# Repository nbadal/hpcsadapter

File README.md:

Breakout Adapter for HP Common Slot Power Supplies
==================================================

This adapter board enables use of an HP (or HPE) Common Slot server power
supply with your 3D printer, cryptocurrency mining rig, etc.  These power
supplies are readily available on the used market at low prices (I've seen
460W models going for just $20) and are more reliable and deliver more power
than the power supplies commonly shipped with 3D printers.

Four pairs of screw terminals provide 12V when the switch is turned on.  A
USB power jack (5V 2.4A) is also provided that is always on when the power
supply is plugged in; this could be used to (for instance) power a Raspberry
Pi running OctoPrint to control your printer.

This project depends on these submodules:

- https://gitlab.com/salfter/kicad-libs
- https://gitlab.com/salfter/digikey-kicad-library

(The latter is a fork of the DigiKey KiCad library at GitHub, with 3D models
added as I need them.)

`git clone --recursive https://gitlab.com/salfter/hpcsadapter.git` should
pull in everything.

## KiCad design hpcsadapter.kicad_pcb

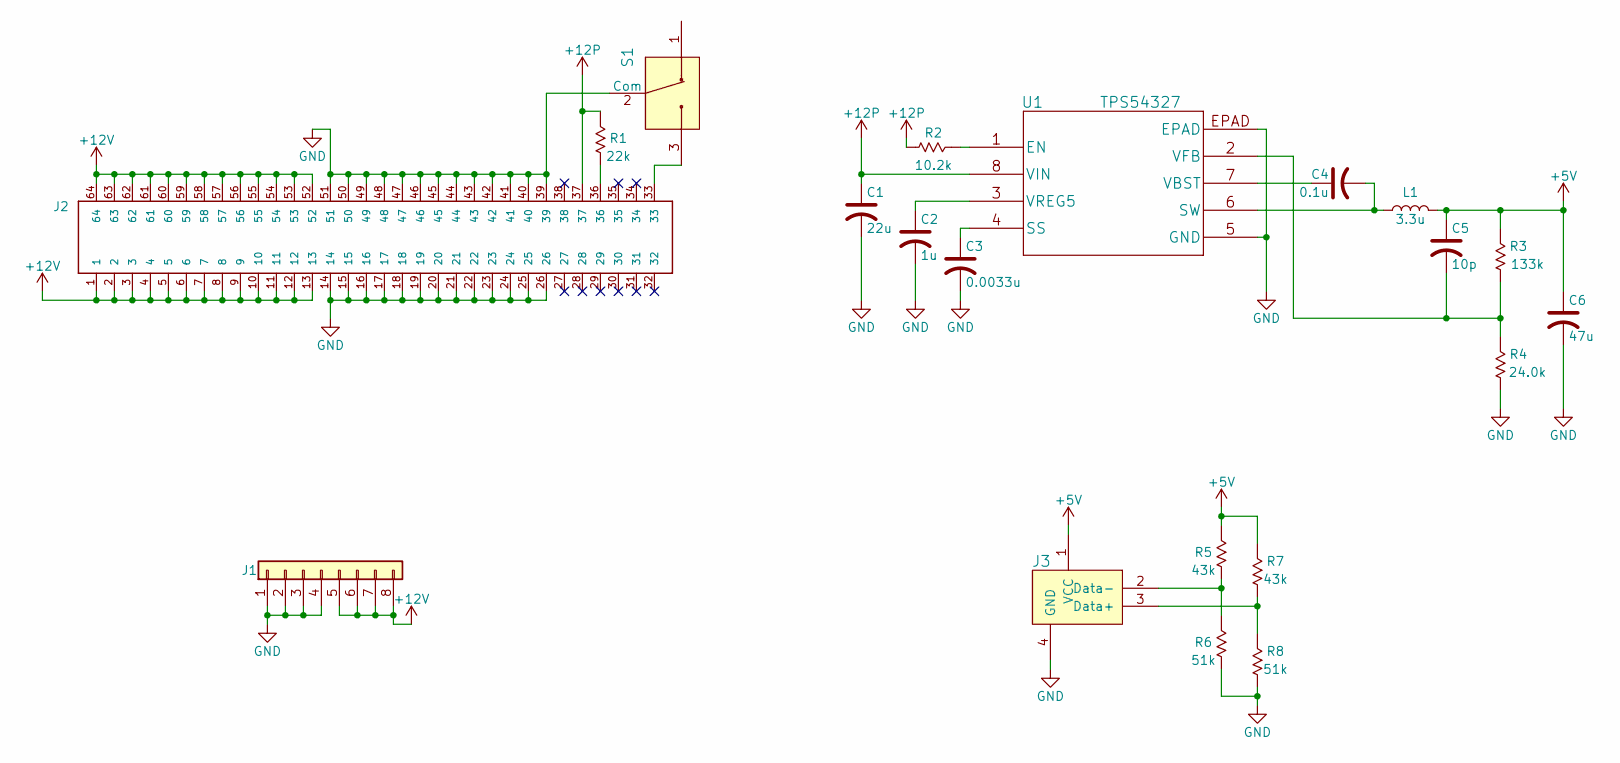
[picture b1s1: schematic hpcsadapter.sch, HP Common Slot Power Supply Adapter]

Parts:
C1: 22u; C_0805; MPN CC0805MKX5R8BB226
C2: 1u; C_0805; MPN CC0805KKX7R8BB105
C3: 0.0033u; C_0805; MPN CC0805KRX7R9BB332
C4: 0.1u; C_0805; MPN CC0805KRX7R8BB104
C5: 10p; C_0805; MPN CC0805JRNPO9BN100
C6: 47u; C_0805; MPN LMK212BBJ476MG-T
J1: OSTYK42108030; Barrier-Block-8pos-TH; MPN OSTYK42108030
J2: 1761469-1; EdgeSocket-64-100mil-TE_1761469-1; MPN 1761469-1
J3: 73725-0110BLF; USB_A_Female_Vertical_RA_73725-0110BLF; MPN 73725-0110BLF
L1: 3.3u; SDR0805-3R3ML; MPN SDR0805-3R3ML
R1: 22k; R_0805; MPN RC0805FR-0722KL
R2: 10.2k; R_0805; MPN RC0805FR-0710K2L
R3: 133k; R_0805; MPN RC0805FR-07133KL
R4: 24.0k; R_0805; MPN RC0805FR-0724KL
R5, R7: 43k; R_0805; MPN RC0805FR-0743KL
R6, R8: 51k; R_0805; MPN RC0805FR-0751KL
S1: 100SP1T1B4M2QE; Toggle_Switch_100SP1T1B4M2QE; MPN 100SP1T1B4M2QE
U1: TPS54327; TPS54327DDAR; MPN TPS54327DDAR

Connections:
+5V: C5.1, C6.1, J3.1 (VCC), L1.2, R3.2, R5.2, R7.2
+12P: C1.1, J2.37, R1.2, R2.1, U1.8 (VIN)
+12V: J1.5, J1.6, J1.7, J1.8, J2.1, J2.2, J2.3, J2.4, J2.5, J2.6, J2.7, J2.8, J2.9, J2.10, J2.11, J2.12, J2.13, J2.52, J2.53, J2.54, J2.55, J2.56, J2.57, J2.58, J2.59, J2.60, J2.61, J2.62, J2.63, J2.64
GND: C1.2, C2.2, C3.2, C6.2, J1.1, J1.2, J1.3, J1.4, J2.14, J2.15, J2.16, J2.17, J2.18, J2.19, J2.20, J2.21, J2.22, J2.23, J2.24, J2.25, J2.26, J2.39, J2.40, J2.41, J2.42, J2.43, J2.44, J2.45, J2.46, J2.47, J2.48, J2.49, J2.50, J2.51, J3.4 (GND), R4.1, R6.1, R8.1, S1.2 (Com), U1.5 (GND), U1.EPAD
unnamed: C2.1, U1.3 (VREG5)
unnamed: C3.1, U1.4 (SS)
unnamed: C4.1, U1.7 (VBST)
unnamed: C4.2, L1.1, U1.6 (SW)
unnamed: C5.2, R3.1, R4.2, U1.2 (VFB)
unnamed: J2.33, S1.3
unnamed: J2.36, R1.1
unnamed: J3.2 (Data-), R5.1, R6.2
unnamed: J3.3 (Data+), R7.1, R8.2
unnamed: R2.2, U1.1 (EN)

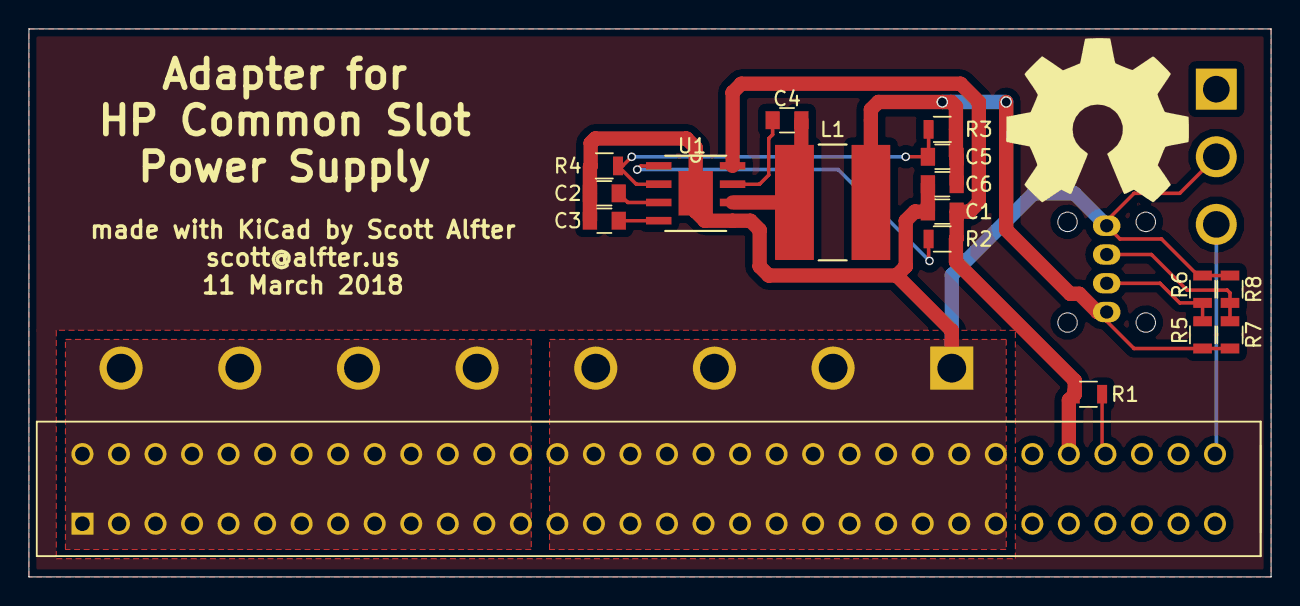
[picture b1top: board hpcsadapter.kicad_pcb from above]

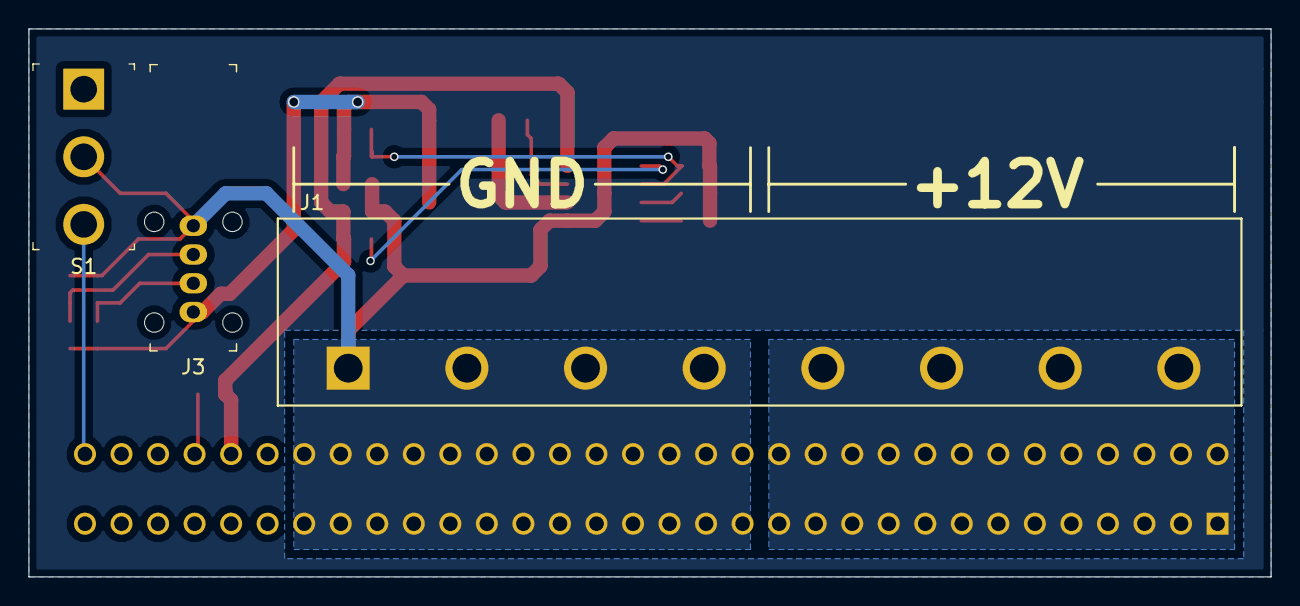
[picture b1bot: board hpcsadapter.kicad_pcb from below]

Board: 2 copper layers, 86.4 x 38.1 mm, 20 parts (3 on the bottom side), 14 nets.

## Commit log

2018-03-09 bare bones...probably ought to add a 5V supply
2018-03-09 some links for later
2018-03-09 another link
2018-03-11 just need to finish tagging components for BOM generation
2018-03-11 BOM completed
2018-03-11 add documentation
2018-03-11 change digikey-kicad-library to point to my fork; fix .gitignore
2018-03-12 USB connector footprint failed DRC...fixed
2018-03-20 separate out non-plated holes

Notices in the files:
parts and their libraries:
Copyright 2016 Accelerated Designs. All rights reserved.
